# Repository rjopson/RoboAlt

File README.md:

# RoboAlt
Repository for hardware, firmware, test code for version 1 altimeter

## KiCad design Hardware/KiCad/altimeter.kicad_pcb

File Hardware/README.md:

# Hardware

Current hardware:
+ Microcontroller - SAMD21G18A-AUT
+ Voltage Regulator - MIC5219-3.3BM5
+ Flash Memory - AT45DB641E
+ Output MOSFET's - DMN2008LFU
+ Speaker - 
+ Sensors:
  + Barometer, thermometer - MS5607
  + Accelerometer (low g) - MPU-6050
  + Accelerometer (high g) - H3LIS331DL

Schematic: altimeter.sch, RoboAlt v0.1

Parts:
C1: 10uF; C_0603
C2, C4, C7, C8, C12, C13, C15, C17: 0.1uF; C_0603
C3: 12.5pF; C_array_2x_0805
C5: 100pF; C_0603
C6: 100mF; PB-5R0H104-R_Super_Capacitor_horizontal
C9: 2.2uF; C_0603
C10: 1uF; C_0603
C11: 10nF; C_0603
C14: 2.2nF; C_0603
C16: 10uF; C_array_2x_0805
D1: Schottky_3; SOT363
D2: LED; LED_0603
L1: 10uH; C_0603
P1, P2: CONN_01X04; SCREWTERMINAL_2.54mm_4
P3, P4: CONN_01X01; 1pin
Q1, Q2, Q3, Q4: DMN2008LFU; 6-UFDFN_Exposed_Pad
R1: 10k; R_array_4x_1206
R2: 100k; R_array_4x_1206
R3: 27k; R_array_4x_1206
R4: 330; R_0603
R5: 10; R_1206
R6: 4.7k; R_array_4x_1206
SP1: SPEAKER; BUZZER_CCV
SW1: SPST; SWITCH_TACTILE_SPST
U1: SAMD21G18A-AUT; TQFP-48_7x7mm_Pitch0.5mm
U2: MIC5219-3.3BM5; SOT23_5
U3: MICRO-B_USB; USB-MICROB
U4: H3LIS331DL; TFLGA-16
U5: MPU-6050; QFN_24
U6: MS5607-02BA03; QFN8_5x3mm
U7: AT45DB641E; SO08_EIAJ
Y1: 32.768kHz; 32khz_crystal

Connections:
+3V3: C1.4, C2.1, C5.2, C7.1, C8.1, C9.1, C11.1, C13.1, C15.2, C16.1, C17.1, D1.1, L1.1, R5.1, R6.1, R6.3, R6.5, SP1.2, U1.17 (VDDIO), U1.36 (VDDIO), U1.44 (VDDIN), U2.5 (VOUT), U4.1 (VDD_IO), U4.8 (CS), U4.14 (VDD), U4.15 (RESERVED), U5.8 (VLOGIC), U5.9 (AD0), U5.13 (VDD), U6.1 (VDD), U6.2 (PS), U6.4 (CSB), U6.5 (CSB), U7.6 (VCC)
+5V: D1.6, U3.1 (VBUS)
+BATT: D1.4, P1.2, P1.3, P2.2, P2.3, R2.1
/3RD: P1.4, Q3.3 (D), R2.7
/A1: R2.2, R3.1, U1.7 (PB08/EIC/AIN2/SCOM4PAD0/TC4)
/A2: R2.6, R3.5, U1.8 (PB09/EIC/AIN3/SCOM4PAD1/TC4)
/A3: R2.4, R3.3, U1.9 (PA04/EIC/REF/AIN4/SCOM0PAD0/TC0)
/A4: R2.8, R3.7, U1.10 (PA05/EIC/AIN5/SCOM0PAD1/TC0)
/APO: P1.1, Q1.3 (D), R2.5
/D2: Q1.1 (G), R1.3, U1.23 (PA14/XIN/EIC/SCOM2PAD2+/TC3)
/D3: Q4.1 (G), R1.5, U1.14 (PA09/I2C/EIC/AIN17/SCOM2PAD1+/TC0)
/D4: Q3.1 (G), R1.1, U1.13 (PA08/I2C/AIN16/SCOM2PAD0+/TC0)
/D6: R1.8, U1.29 (PA20/EIC/SCOM5PAD2+)
/D7: U1.30 (PA21/EIC/SCOM5PAD3+), U7.5 (WP)
/D8: U1.11 (PA06/EIC/AIN6/SCOM0PAD2/TC1), U7.3 (RESET)
/DATA+: U1.34 (PA25/EIC/SCOM3PAD3+/TC5), U3.3 (D+)
/DATA-: U1.33 (PA24/EIC/SCOM3PAD2+/TC5), U3.2 (D-)
/MAIN: P2.1, Q4.3 (D), R2.3
/MISO: U1.21 (PA12/I2C/EIC/SCOM2PAD0+/TC2), U7.8 (SO)
/MOSI: U1.19 (PB10/EIC/SCOM4PAD2/TC5), U7.1 (SI)
/RESET: C5.1, R4.2, U1.40 (RESETN)
/SCK: U1.20 (PB11/EIC/SCOM4PAD3/TC5), U7.2 (SCK)
/SCL: R6.2, U1.32 (PA23/I2C/EIC/SCOM5PAD1+/TC4), U4.4 (SCL/SPC), U5.23 (SCL), U6.8 (SCLK)
/SDA: R6.4, U1.31 (PA22/I2C/EIC/SCOM5PAD0+/TC4), U4.6 (SDA/SDI/SDO), U5.24 (SDA), U6.7 (SDI/SDA)
/SS: U1.27 (PA18/EIC/SCOM1PAD2+/TC3), U7.4 (CS)
GND: C1.1, C1.3, C2.2, C3.2, C3.4, C4.2, C6.2, C7.2, C8.2, C9.2, C10.2, C11.2, C12.2, C13.2, C14.1, C15.1, C16.2, C17.2, D2.1 (K), P2.4, Q1.2 (S), Q2.2 (S), Q3.2 (S), Q4.2 (S), R1.2, R1.4, R1.6, R3.2, R3.4, R3.6, R3.8, SW1.1, U1.5 (GNDANA), U1.18 (GND), U1.35 (GND), U1.42 (GND), U2.2 (GND), U3.5 (GND), U4.5 (GND), U4.7 (SDO/SDA0), U4.10 (RESERVED), U4.12 (GND), U4.13 (GND), U4.16 (GND), U5.1 (CLKIN), U5.11 (FSYNC), U5.18 (GND), U6.3 (GND), U7.7 (GND)
unnamed: C1.2, C4.1, L1.2, U1.6 (VDDANA)
unnamed: C3.1, U1.1 (PA00/XIN32/EIC/SCOM1PAD0/TC2), Y1.1
unnamed: C3.3, U1.2 (PA01/XOUT32/EIC/SCOM1PAD1/TC2), Y1.2
unnamed: C6.1, R5.2
unnamed: C10.1, U1.43 (VDDCORE)
unnamed: C12.1, U5.10 (REGOUT)
unnamed: C14.2, U5.20 (CPOUT)
unnamed: D1.2, Q2.3 (D), SP1.1
unnamed: D1.3, D1.5, U2.1 (VIN), U2.3 (ENABLE)
unnamed: D2.2 (A), R6.6
unnamed: Q2.1 (G), R1.7
unnamed: R4.1, SW1.2

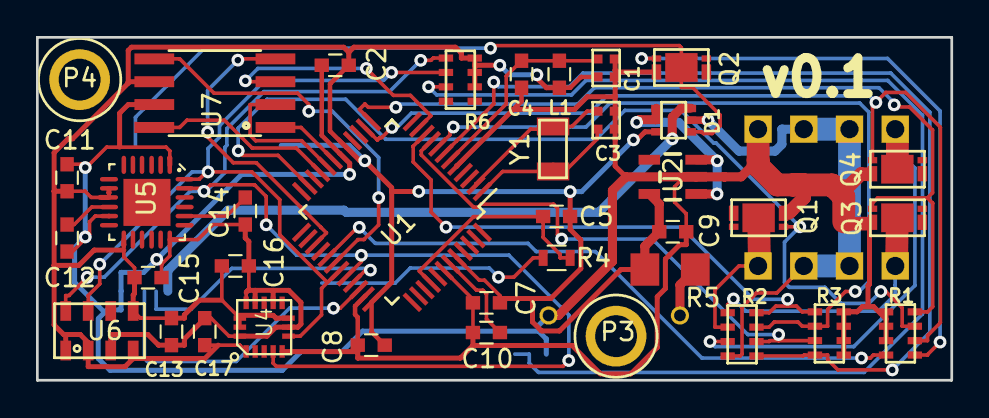
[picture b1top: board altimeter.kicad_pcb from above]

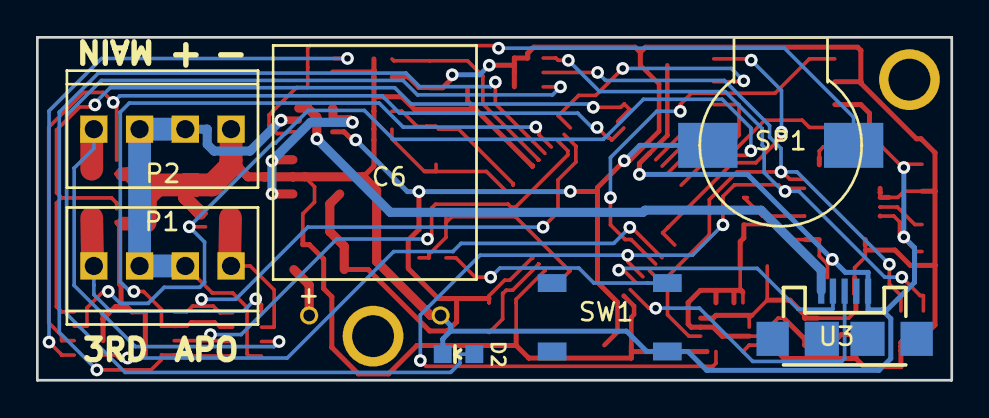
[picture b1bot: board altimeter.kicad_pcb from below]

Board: 2 copper layers, 50.8 x 19.0 mm, 44 parts (7 on the bottom side), 38 nets.

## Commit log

2018-10-18 initialize remote repository
2018-10-18 importing project
2018-10-18 added I2C, MS5607 classes
2018-10-18 cleanup on MS5607 header
2018-10-18 merged README with local directory
2018-10-18 transferred full I2C library over
2018-10-18 Complete MS5607 library to pull raw pressure, temp data
2018-10-18 Add MPU6050 class (16 accelerometer/gyro)
2018-10-18 add H3LIS331DL 200 g accelerometer
2018-10-19 Implement IMU class
2018-10-20 added IMU unit tests
2018-10-20 implement barometer class, altitude class and unit tests for both
2018-10-20 moved sensor classes to driver folder
2018-10-21 added AT45DB641 driver and pins.h
2018-10-21 add erase function to AT45DB641
2018-10-21 added buzzer class
2018-10-21 added pyro class
2018-10-25 added flight logic, cleaned up errors with includes in pyro
2018-10-25 add flightRecord class to track data to be recorded
2018-11-05 added dataStorage
2018-11-05 add user settings management
2018-11-20 added dataStructures and manageSensors
2018-11-20 Added matrixMath class - simple matrix math object and operations
2018-11-20 begin matrixMath unit tests
2018-11-21 unit testing and debugging of matrixMath
2018-11-23 Kalman filter added
2018-11-23 Kalman class imlementation
2018-11-23 cleaning up Kalman implementation
2018-11-23 corrected conversion back to fixed point output
2018-11-24 Reduce oversampling rate of MS5607 to lowest
2018-11-24 added manageDataReduction
2018-11-25 processData class added to manage sensor conversion to engineering units, data filtering
2018-11-25 correct I2C read to replace timeout functionality. Not needed because Wire.requestFrom takes care of this.
2018-11-25 begin implementing flight data storage functionality
2018-11-25 begin main sensorAndControl for all sensor drivers and data reduction
2018-11-26 Implement manageSensorsAndControl class
2018-11-26 data processing project added - will test manageSensorsAndControl loop using text files of test data
2018-11-30 Setup for includes in data test loop
2018-12-12 begin dataIO for read/write to flight data file. For testing
2018-12-15 test data added, dataIO read function work
2018-12-16 dataIO read/write functionality implemented. Folder of flight test data added
2018-12-16 convert state data to mm, Kalman class debugged
2019-02-11 Added new KiCad project with .sch and _pcb files
2019-02-11 Update hardware file structure
2019-02-11 Added KiCad schematic component library
2019-02-11 add KiCad footprints
2019-02-11 Major components added to schematic
2019-02-11 Reorganize Hardware folder
2019-02-18 Pyro output, regulator and buzzer schematics created
2019-02-25 Schematic - sensors connected
2019-02-25 combine resistors into arrays
2019-02-25 Component and footprint association
2019-02-25 Create pcb with all components
2019-04-08 board connected
2019-04-08 convert flightLogic to enum
2019-04-09 flightDataStorage implemented
2019-04-10 buzzer startup functionality, pyro class cleanup
2019-06-06 test from LAP47
2019-06-07 Revert "test from LAP47"
    This reverts commit 4f6db638a1aa868f051f523a0b7e3e81e07de3c4.
2019-06-15 Board v0.1 ordered
2019-06-17 add python plotting script for processData
2019-09-04 Sod Blaster Tri Cities 2019 - clean code, hardware
2019-09-21 Interface program development
2019-10-08 Interface development, simulation and post processing development, start h5 database
2019-10-16 before instance implementation
2019-10-22 hdf5 export complete
2019-10-31 event control of simulation implementation started
2019-11-04 Flight events implemented in simulation engine. Added file write for events
2019-11-04 before flight_phase functionality changes
2019-11-04 save before flight_phase test2
2019-11-22 pull simulation data from engine
2019-11-22 before enum refactor
2019-12-13 before replacing interface core with cpp
2020-02-02 Initial cpp interface core implementation
2020-02-08 before testing std::function
2020-02-14 work on supporting stages
2020-02-27 SimulationStage concept
2020-03-02 simulation solver function
2020-03-06 refactor to place drag calcs in stage
2020-03-13 before style cleanup, changes to be usable with Cython
2020-03-14 after style cleanup
2020-03-20 for AZ
2020-04-01 hide pointer vectors in entity classes
2020-04-04 entity inheritance test
2020-04-05 after entity base class conversion
2020-04-07 before cleanup of user events, sim stages in simulation
2020-04-08 after simulation cleanup
2020-04-11 before inheritance for part in python
2020-04-12 database scripting wrap working in python
2020-04-12 solution structure cleanup
2020-04-12 directory cleanup
2020-04-13 clearing directory
2020-04-13 replaced
2020-04-13 project cleanup
2020-04-13 cython running again
2020-04-13 matched script test to cpp api
2020-04-14 object list output in python
2020-04-15 entity_manager returns pointers to created entities now
2020-04-16 hdf5 read_write
2020-04-19 before messing with rk45 for results save
2020-04-29 before removal of sim stage
2020-04-29 after removal of experimental-stage and simulation_stage
2020-05-10 conversion to pybind11 for core python code
2020-05-10 before adding set_attributes to entity create functions
2020-05-12 hdf5 read/write complete
2020-05-12 corrected default motor name
